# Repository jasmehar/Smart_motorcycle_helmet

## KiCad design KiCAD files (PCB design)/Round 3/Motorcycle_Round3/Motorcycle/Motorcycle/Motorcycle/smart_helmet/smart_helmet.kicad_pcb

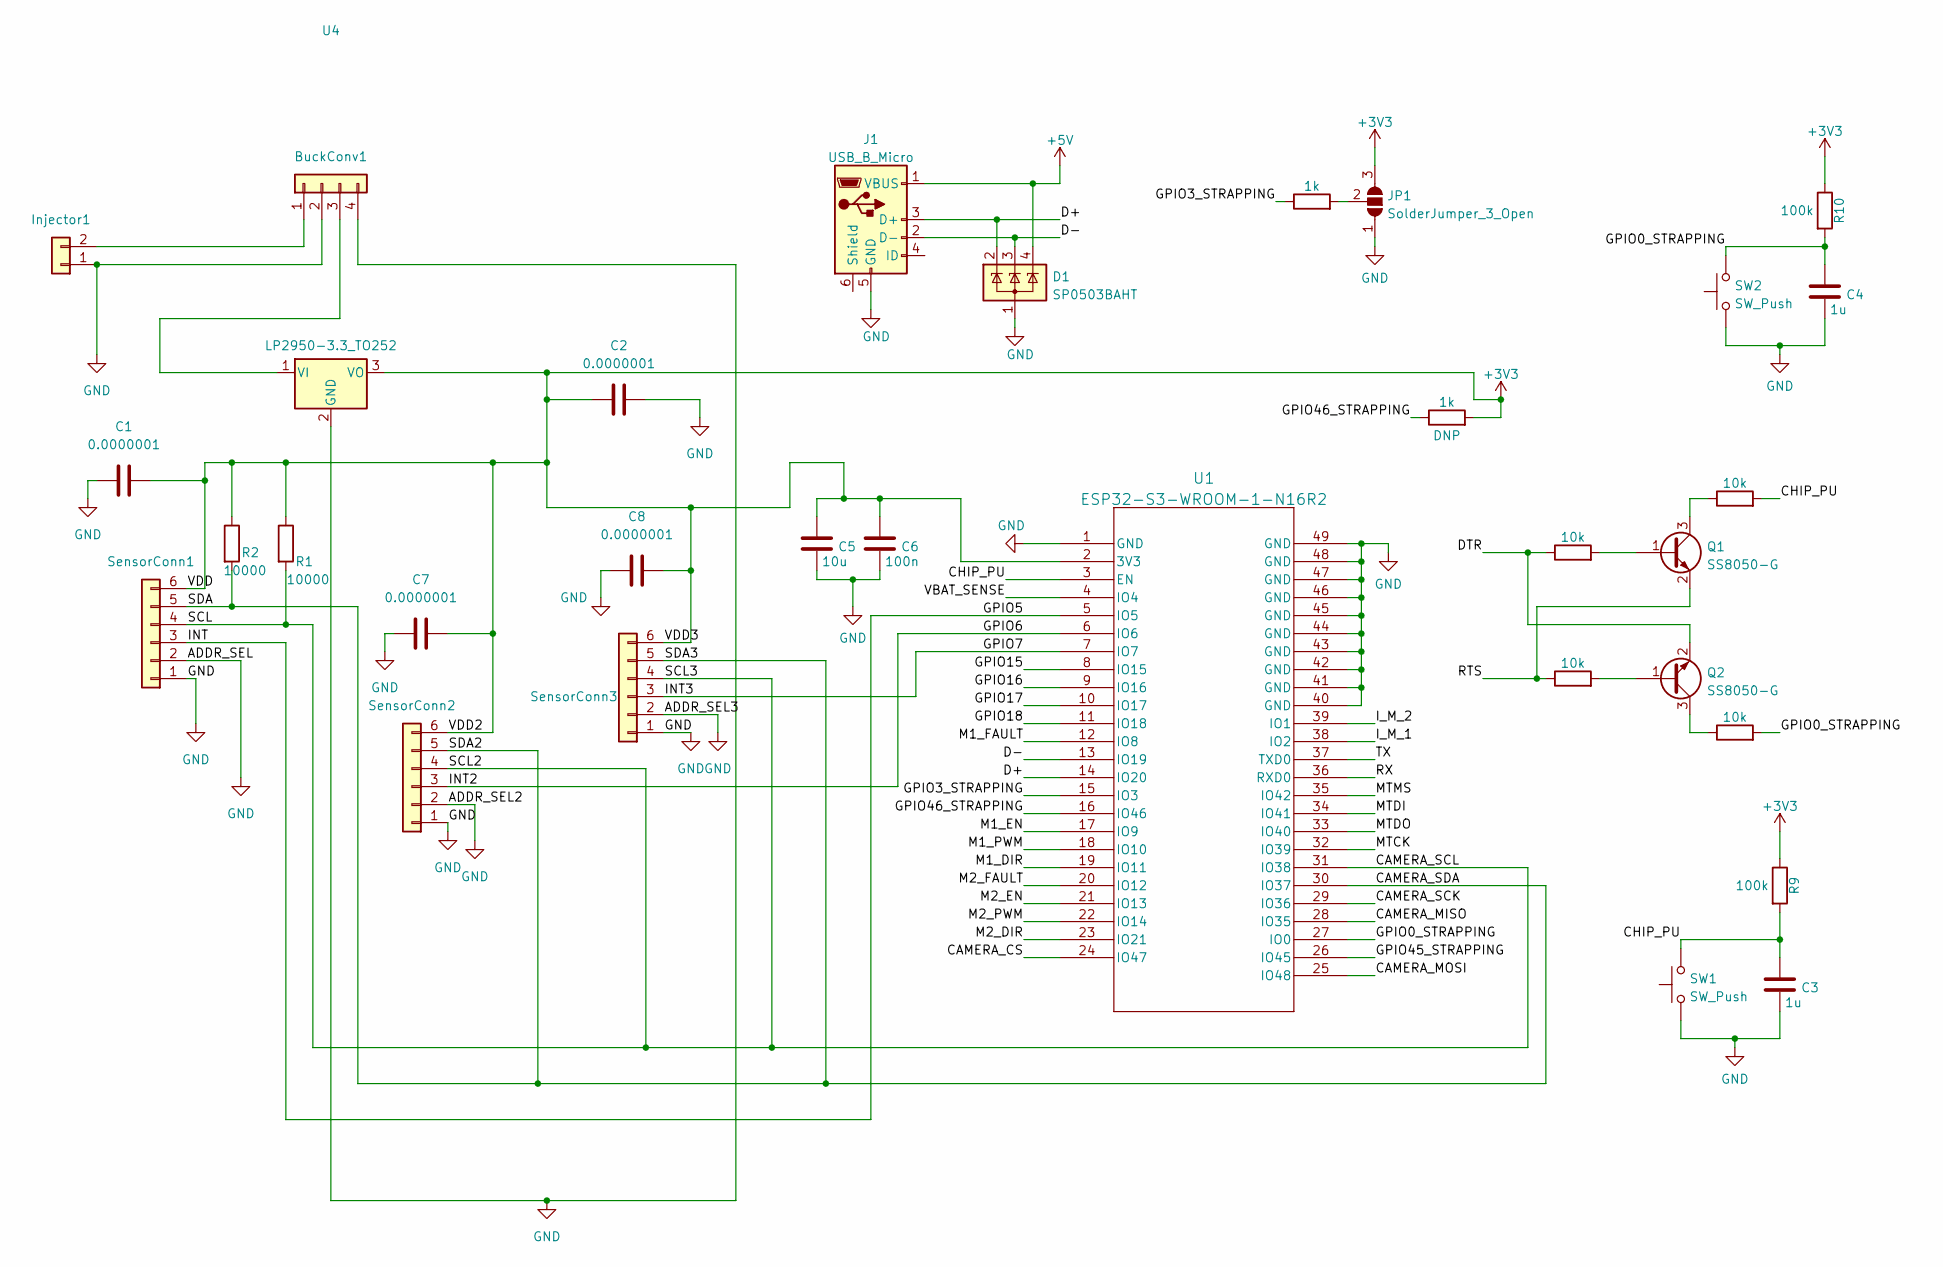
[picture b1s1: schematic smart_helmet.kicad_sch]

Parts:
BuckConv1: Conn_01x04; Molex_KK-254_AE-6410-04A_1x04_P2.54mm_Vertical
C1, C2, C7, C8: 0.0000001; C_0805_2012Metric_Pad1.18x1.45mm_HandSolder
C3, C4: 1u; C_0805_2012Metric
C5: 10u; C_0805_2012Metric
C6: 100n; C_0805_2012Metric
D1: SP0503BAHT; SOT-143
Injector1: Conn_01x02; Molex_KK-254_AE-6410-02A_1x02_P2.54mm_Vertical
J1: USB_B_Micro; USB_Micro-B_Amphenol_10118194_Horizontal
JP1: SolderJumper_3_Open; SolderJumper-3_P2.0mm_Open_TrianglePad1.0x1.5mm
Q1, Q2: SS8050-G; SOT-23
R1, R2: 10000; R_0805_2012Metric_Pad1.20x1.40mm_HandSolder
R3, R6: 1k; R_0805_2012Metric
R4, R5, R7, R8: 10k; R_0805_2012Metric
R9, R10: 100k; R_0805_2012Metric
SW1, SW2: SW_Push; SW_SPST_B3S-1000
SensorConn1, SensorConn2, SensorConn3: Conn_01x06; Molex_KK-254_AE-6410-06A_1x06_P2.54mm_Vertical
U1: ESP32-S3-WROOM-1-N16R2; ESP32-S3-WROOM-1_EXP
U4: LP2950-3.3_TO252; LP3_TEX

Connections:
+3V3: C1.1, C2.1, C5.1, C6.1, C7.1, C8.1, JP1.3 (B), R1.1, R2.1, R3.2, R9.1, R10.1, SensorConn1.6, SensorConn2.6, SensorConn3.6, U1.2 (3V3), U4.3 (VO)
+5V: D1.4 (K), J1.1 (VBUS)
/CAMERA_CS: U1.24 (IO47)
/CAMERA_MISO: U1.28 (IO35)
/CAMERA_MOSI: U1.25 (IO48)
/CAMERA_SCK: U1.29 (IO36)
/CAMERA_SCL: R1.2, SensorConn1.4, SensorConn2.4, SensorConn3.4, U1.31 (IO38)
/CAMERA_SDA: R2.2, SensorConn1.5, SensorConn2.5, SensorConn3.5, U1.30 (IO37)
/CHIP_PU: C3.1, R7.2, R9.2, SW1.2, U1.3 (EN)
/D+: D1.2 (K), J1.3 (D+), U1.14 (IO20)
/D-: D1.3 (K), J1.2 (D-), U1.13 (IO19)
/DTR: Q2.2 (E), R4.1
/GPIO0_STRAPPING: C4.1, R8.2, R10.2, SW2.2, U1.27 (IO0)
/GPIO3_STRAPPING: R6.1, U1.15 (IO3)
/GPIO5: SensorConn1.3, U1.5 (IO5)
/GPIO6: SensorConn2.3, U1.6 (IO6)
/GPIO7: SensorConn3.3, U1.7 (IO7)
/GPIO15: U1.8 (IO15)
/GPIO16: U1.9 (IO16)
/GPIO17: U1.10 (IO17)
/GPIO18: U1.11 (IO18)
/GPIO45_STRAPPING: U1.26 (IO45)
/GPIO46_STRAPPING: R3.1, U1.16 (IO46)
/I_M_1: U1.38 (IO2)
/I_M_2: U1.39 (IO1)
/M1_DIR: U1.19 (IO11)
/M1_EN: U1.17 (IO9)
/M1_FAULT: U1.12 (IO8)
/M1_PWM: U1.18 (IO10)
/M2_DIR: U1.23 (IO21)
/M2_EN: U1.21 (IO13)
/M2_FAULT: U1.20 (IO12)
/M2_PWM: U1.22 (IO14)
/MTCK: U1.32 (IO39)
/MTDI: U1.34 (IO41)
/MTDO: U1.33 (IO40)
/MTMS: U1.35 (IO42)
/RTS: Q1.2 (E), R5.1
/RX: U1.36 (RXD0)
/TX: U1.37 (TXD0)
/VBAT_SENSE: U1.4 (IO4)
GND: BuckConv1.2, BuckConv1.4, C1.2, C2.2, C3.2, C4.2, C5.2, C6.2, C7.2, C8.2, D1.1 (A), Injector1.1, J1.5 (GND), JP1.1 (A), SW1.1, SW2.1, SensorConn1.1, SensorConn1.2, SensorConn2.1, SensorConn2.2, SensorConn3.1, SensorConn3.2, U1.1 (GND), U1.40 (GND), U1.41 (GND), U1.42 (GND), U1.43 (GND), U1.44 (GND), U1.45 (GND), U1.46 (GND), U1.47 (GND), U1.48 (GND), U1.49 (GND), U4.2 (GND)
unnamed: BuckConv1.1, Injector1.2
unnamed: BuckConv1.3, U4.1 (VI)
unnamed: JP1.2 (C), R6.2
unnamed: Q1.1 (B), R4.2
unnamed: Q1.3 (C), R7.1
unnamed: Q2.1 (B), R5.2
unnamed: Q2.3 (C), R8.1

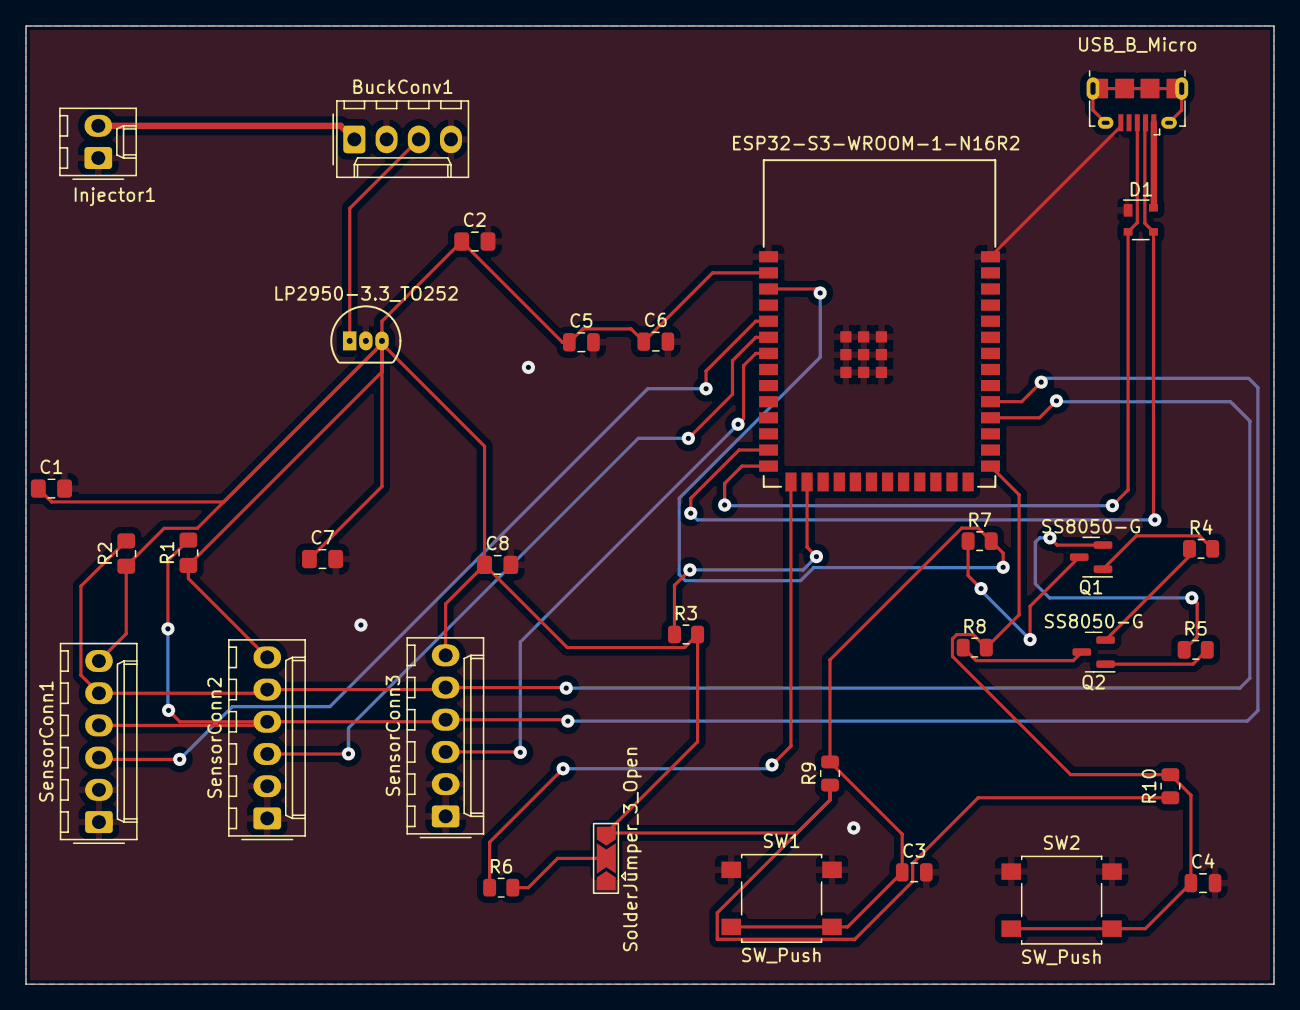
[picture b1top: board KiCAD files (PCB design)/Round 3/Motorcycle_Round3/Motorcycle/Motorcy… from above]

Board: 2 copper layers, 98.4 x 75.6 mm, 32 parts (0 on the bottom side), 23 nets.

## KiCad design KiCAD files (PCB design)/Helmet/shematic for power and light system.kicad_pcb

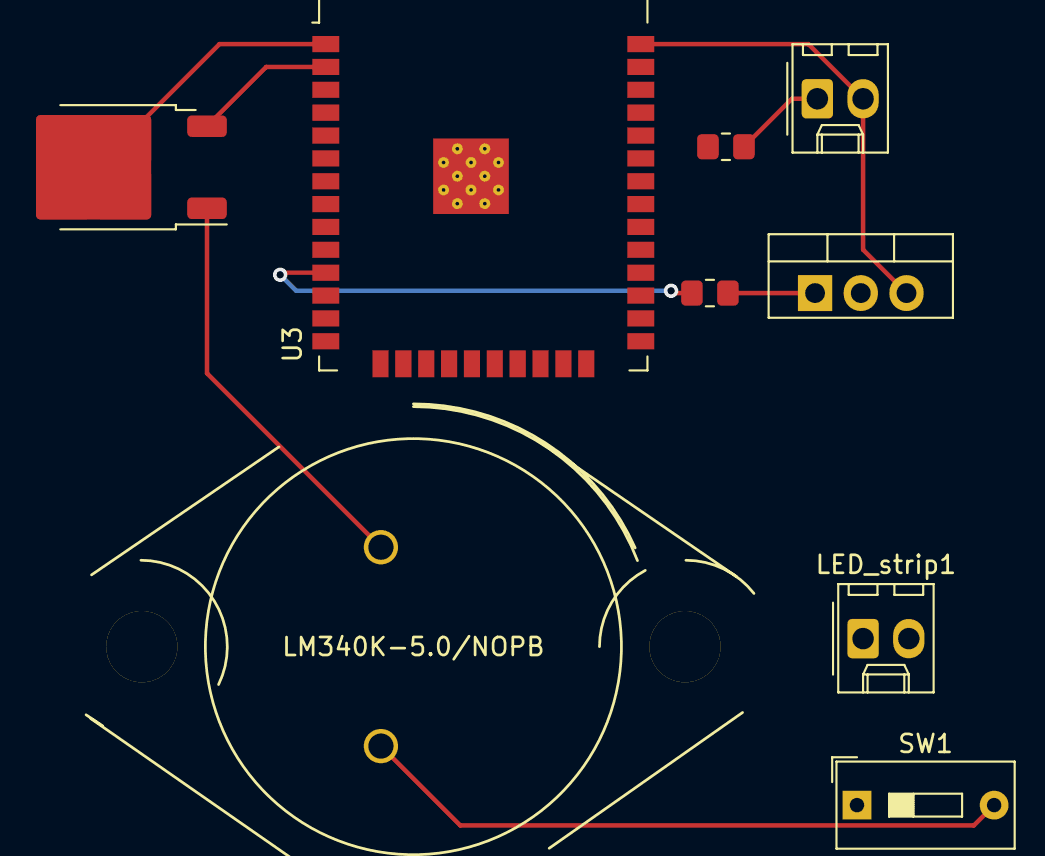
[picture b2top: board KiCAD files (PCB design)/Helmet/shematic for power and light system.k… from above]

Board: 2 copper layers, 9 parts (0 on the bottom side), 8 nets.

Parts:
J1: LED; Molex_KK-254_AE-6410-02A_1x02_P2.54mm_Vertical
LED_strip1: Molex_KK-254_AE-6410-02A_1x02_P2.54mm_Vertical
Q1: IRLZ44N; TO-220-3_Vertical
R1, R2: R; R_0805_2012Metric_Pad1.20x1.40mm_HandSolder
SW1: SW_DIP_x01; SW_DIP_SPSTx01_Slide_9.78x4.72mm_W7.62mm_P2.54mm
U1: LM340K-5.0/NOPB; LM340K-5.0&slash_NOPB
U2: LP2950-3.3_TO252; TO-252-2
U3: ESP32-WROOM-32

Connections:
GND: J1.2, Q1.3 (S), U1.3 (GND), U2.2 (GND), U3.1 (GND), U3.15 (GND), U3.38 (GND), U3.39 (GND)
unnamed: J1.1, R2.2
unnamed: Q1.1 (G), R1.2
unnamed: SW1.2, U1.1 (IN)
unnamed: U1.2 (OUT), U2.1 (VI)
unnamed: U2.3 (VO), U3.2 (VDD)
unnamed: R2.1, U3.37 (IO23)
unnamed: R1.1, U3.11 (IO26)

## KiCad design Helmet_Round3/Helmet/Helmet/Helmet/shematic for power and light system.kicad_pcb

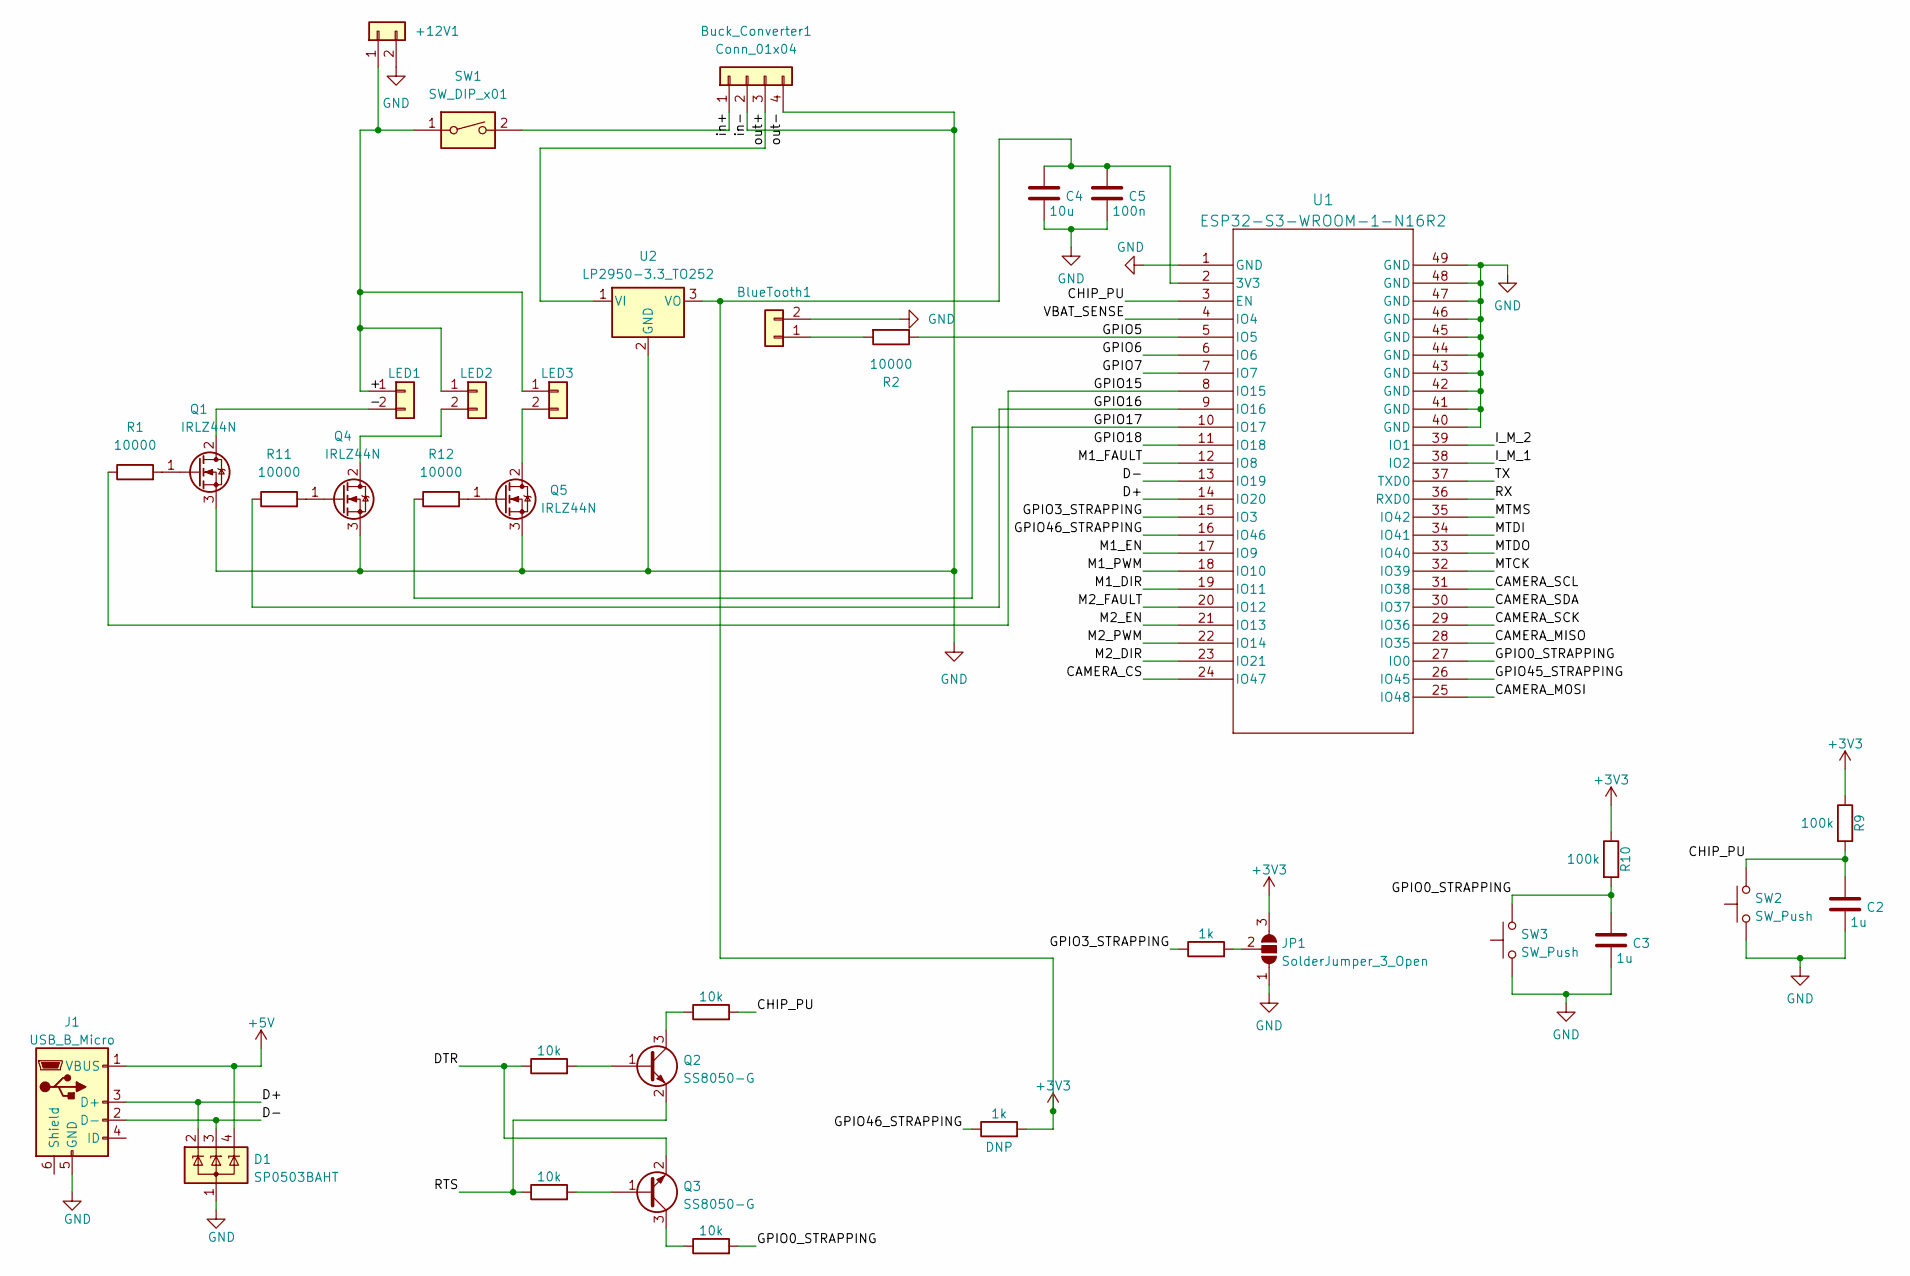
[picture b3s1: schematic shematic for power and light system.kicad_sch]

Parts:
+12V1: Conn_01x02; Molex_KK-254_AE-6410-02A_1x02_P2.54mm_Vertical
BlueTooth1: LED; Molex_KK-254_AE-6410-02A_1x02_P2.54mm_Vertical
Buck_Converter1: Conn_01x04; Molex_KK-254_AE-6410-04A_1x04_P2.54mm_Vertical
C2, C3: 1u; C_0805_2012Metric
C4: 10u; C_0805_2012Metric
C5: 100n; C_0805_2012Metric
D1: SP0503BAHT; SOT-143
J1: USB_B_Micro; USB_Micro-B_Amphenol_10118194_Horizontal
JP1: SolderJumper_3_Open; SolderJumper-3_P2.0mm_Open_TrianglePad1.0x1.5mm
LED1, LED2, LED3: Conn_01x02; Molex_KK-254_AE-6410-02A_1x02_P2.54mm_Vertical
Q1, Q4, Q5: IRLZ44N; PG-TO220-3_INF
Q2, Q3: SS8050-G; SOT-23
R1, R2, R11, R12: 10000; R_0805_2012Metric_Pad1.20x1.40mm_HandSolder
R3, R6: 1k; R_0805_2012Metric
R4, R5, R7, R8: 10k; R_0805_2012Metric
R9, R10: 100k; R_0805_2012Metric
SW1: SW_DIP_x01; SW_DIP_SPSTx01_Slide_9.78x4.72mm_W7.62mm_P2.54mm
SW2, SW3: SW_Push; SW_SPST_B3S-1000
U1: ESP32-S3-WROOM-1-N16R2; ESP32-S3-WROOM-1_EXP
U2: LP2950-3.3_TO252; LP3_TEX

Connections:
+3V3: C4.1, C5.1, JP1.3 (B), R3.2, R9.1, R10.1, U1.2 (3V3), U2.3 (VO)
+5V: D1.4 (K), J1.1 (VBUS)
/+: +12V1.1, LED1.1, LED2.1, LED3.1, SW1.1
/-: LED1.2, Q1.2 (D)
/CAMERA_CS: U1.24 (IO47)
/CAMERA_MISO: U1.28 (IO35)
/CAMERA_MOSI: U1.25 (IO48)
/CAMERA_SCK: U1.29 (IO36)
/CAMERA_SCL: U1.31 (IO38)
/CAMERA_SDA: U1.30 (IO37)
/CHIP_PU: C2.1, R7.2, R9.2, SW2.2, U1.3 (EN)
/D+: D1.2 (K), J1.3 (D+), U1.14 (IO20)
/D-: D1.3 (K), J1.2 (D-), U1.13 (IO19)
/DTR: Q3.2 (E), R4.1
/GPIO0_STRAPPING: C3.1, R8.2, R10.2, SW3.2, U1.27 (IO0)
/GPIO3_STRAPPING: R6.1, U1.15 (IO3)
/GPIO5: R2.1, U1.5 (IO5)
/GPIO6: U1.6 (IO6)
/GPIO7: U1.7 (IO7)
/GPIO15: R1.1, U1.8 (IO15)
/GPIO16: R11.1, U1.9 (IO16)
/GPIO17: R12.1, U1.10 (IO17)
/GPIO18: U1.11 (IO18)
/GPIO45_STRAPPING: U1.26 (IO45)
/GPIO46_STRAPPING: R3.1, U1.16 (IO46)
/I_M_1: U1.38 (IO2)
/I_M_2: U1.39 (IO1)
/M1_DIR: U1.19 (IO11)
/M1_EN: U1.17 (IO9)
/M1_FAULT: U1.12 (IO8)
/M1_PWM: U1.18 (IO10)
/M2_DIR: U1.23 (IO21)
/M2_EN: U1.21 (IO13)
/M2_FAULT: U1.20 (IO12)
/M2_PWM: U1.22 (IO14)
/MTCK: U1.32 (IO39)
/MTDI: U1.34 (IO41)
/MTDO: U1.33 (IO40)
/MTMS: U1.35 (IO42)
/RTS: Q2.2 (E), R5.1
/RX: U1.36 (RXD0)
/TX: U1.37 (TXD0)
/VBAT_SENSE: U1.4 (IO4)
/in+: Buck_Converter1.1, SW1.2
/out+: Buck_Converter1.3, U2.1 (VI)
GND: +12V1.2, BlueTooth1.2, Buck_Converter1.2, Buck_Converter1.4, C2.2, C3.2, C4.2, C5.2, D1.1 (A), J1.5 (GND), JP1.1 (A), Q1.3 (S), Q4.3 (S), Q5.3 (S), SW2.1, SW3.1, U1.1 (GND), U1.40 (GND), U1.41 (GND), U1.42 (GND), U1.43 (GND), U1.44 (GND), U1.45 (GND), U1.46 (GND), U1.47 (GND), U1.48 (GND), U1.49 (GND), U2.2 (GND)
unnamed: BlueTooth1.1, R2.2
unnamed: JP1.2 (C), R6.2
unnamed: LED2.2, Q4.2 (D)
unnamed: LED3.2, Q5.2 (D)
unnamed: Q1.1 (G), R1.2
unnamed: Q2.1 (B), R4.2
unnamed: Q2.3 (C), R7.1
unnamed: Q3.1 (B), R5.2
unnamed: Q3.3 (C), R8.1
unnamed: Q4.1 (G), R11.2
unnamed: Q5.1 (G), R12.2

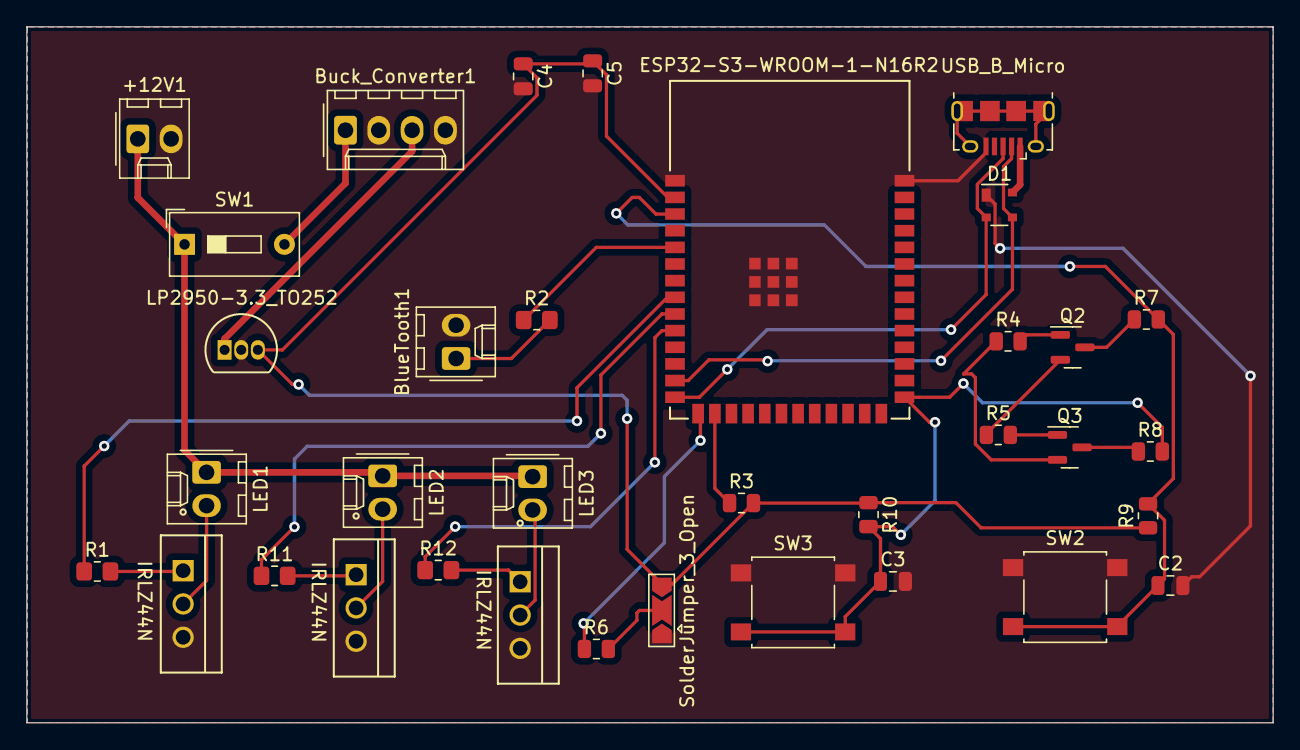
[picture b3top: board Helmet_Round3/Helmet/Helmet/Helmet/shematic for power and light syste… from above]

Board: 2 copper layers, 95.0 x 53.1 mm, 35 parts (0 on the bottom side), 30 nets.

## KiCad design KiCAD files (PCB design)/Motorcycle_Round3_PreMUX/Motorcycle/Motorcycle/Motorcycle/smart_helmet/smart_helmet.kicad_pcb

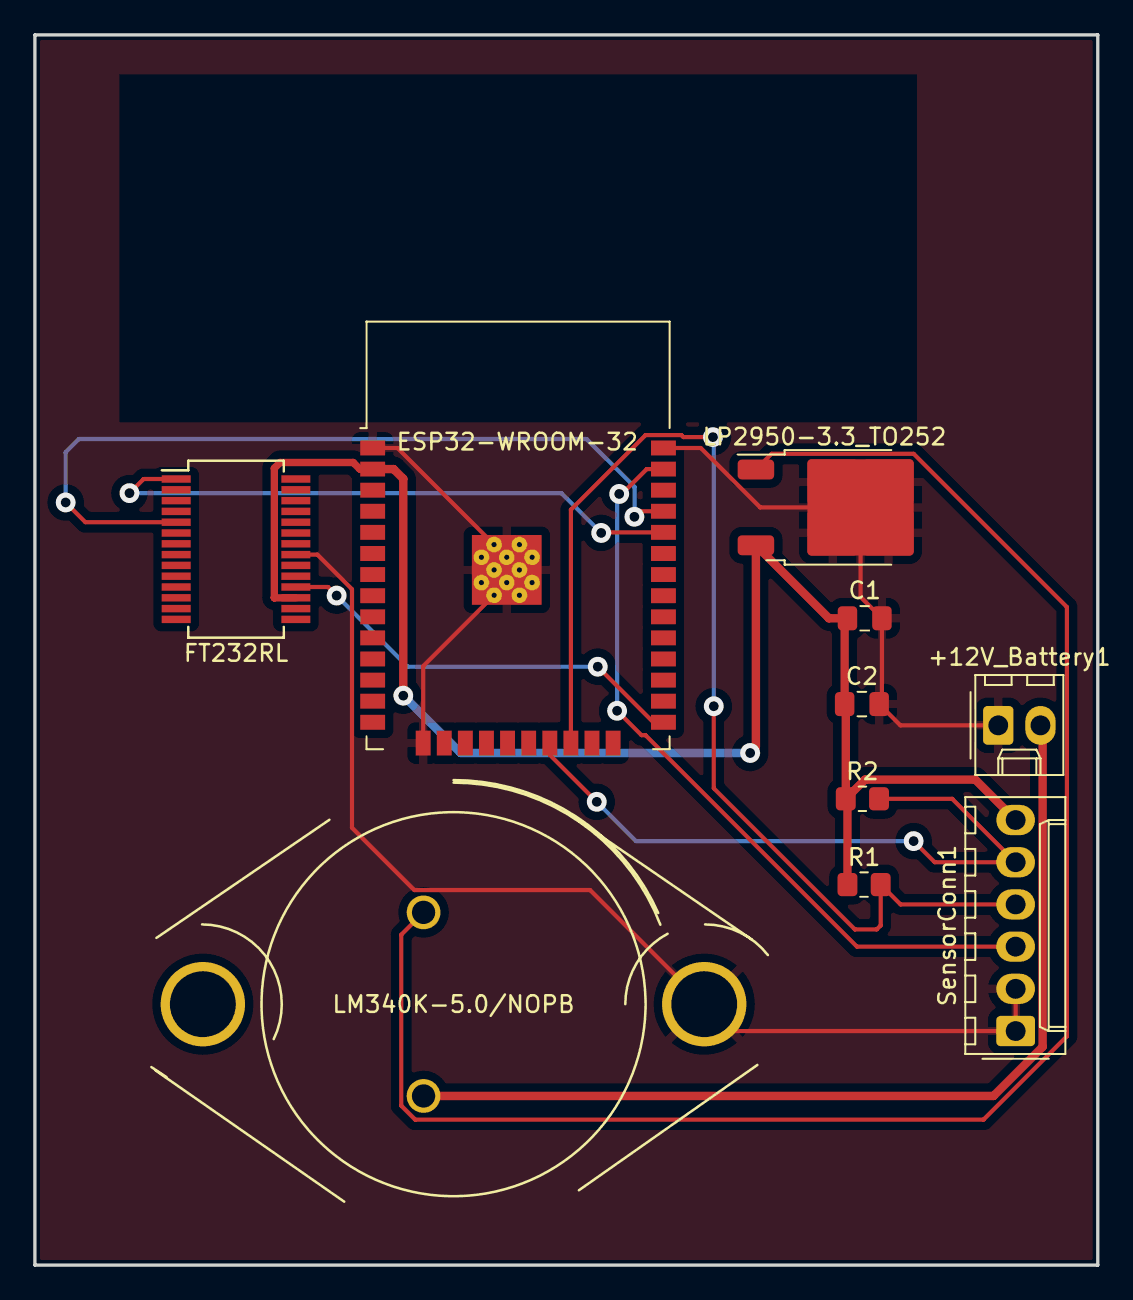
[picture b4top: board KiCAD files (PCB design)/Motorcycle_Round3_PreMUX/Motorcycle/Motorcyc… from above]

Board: 2 copper layers, 64.0 x 74.0 mm, 10 parts (0 on the bottom side), 10 nets.

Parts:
+12V_Battery1: Conn_01x02; Molex_KK-254_AE-6410-02A_1x02_P2.54mm_Vertical
C1, C2: 0.0000001; C_0805_2012Metric_Pad1.18x1.45mm_HandSolder
R1, R2: 10000; R_0805_2012Metric_Pad1.20x1.40mm_HandSolder
SensorConn1: Conn_01x06; Molex_KK-254_AE-6410-06A_1x06_P2.54mm_Vertical
U1: FT232RL; SSOP-28_5.3x10.2mm_P0.65mm
U3: LM340K-5.0/NOPB; LM340K-5.0&slash_NOPB
U4: LP2950-3.3_TO252; TO-252-2
U5: ESP32-WROOM-32

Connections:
/INT: SensorConn1.3, U5.37 (IO23)
/SCL: R1.2, SensorConn1.4, U5.22 (SDI/SD1)
/SDA: R2.2, SensorConn1.5, U5.21 (SDO/SD0)
/VDD: C1.1, C2.1, R1.1, R2.1, SensorConn1.6, U1.17 (3V3OUT), U4.3 (VO), U5.2 (VDD)
GND: +12V_Battery1.1, C1.2, C2.2, SensorConn1.1, SensorConn1.2, U1.21 (GND), U3.3 (GND), U4.2 (GND), U5.1 (GND), U5.15 (GND), U5.38 (GND), U5.39 (GND)
unnamed: +12V_Battery1.2, U3.1 (IN)
unnamed: U1.5 (RXD), U5.35 (TXD0/IO1)
unnamed: U1.1 (TXD), U5.34 (RXD0/IO3)
unnamed: U3.2 (OUT), U4.1 (VI)
unnamed: U1.18 (GND), U5.25 (IO0)

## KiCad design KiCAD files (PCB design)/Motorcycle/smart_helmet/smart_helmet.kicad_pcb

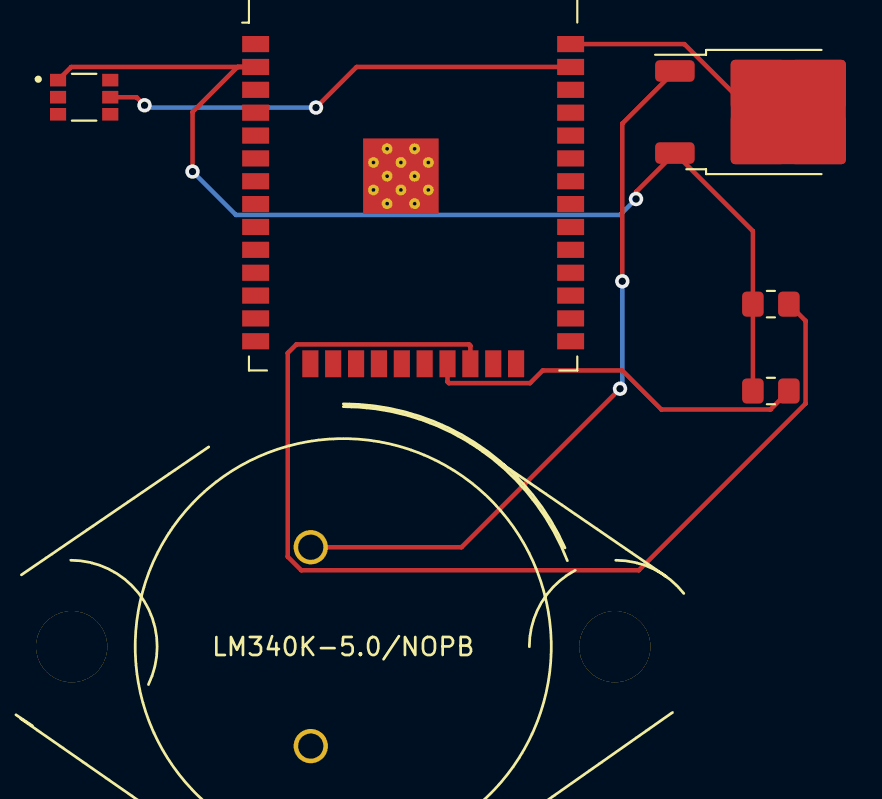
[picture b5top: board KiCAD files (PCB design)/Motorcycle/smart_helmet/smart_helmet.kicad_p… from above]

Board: 2 copper layers, 6 parts (0 on the bottom side), 6 nets.

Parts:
R1, R2: 10000; R_0805_2012Metric_Pad1.20x1.40mm_HandSolder
U2: TSL2561; XDCR_TSL2561
U3: LM340K-5.0/NOPB; LM340K-5.0&slash_NOPB
U4: LP2950-3.3_TO252; TO-252-2
U5: ESP32-WROOM-32

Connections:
GND: U2.2 (ADDR_SEL), U2.3 (GND), U3.3 (GND), U4.2 (GND), U5.1 (GND), U5.15 (GND), U5.38 (GND), U5.39 (GND)
unnamed: U2.5 (INT), U5.37 (IO23)
unnamed: R1.2, U2.4 (SCL), U5.22 (SDI/SD1)
unnamed: R2.2, U2.6 (SDA), U5.21 (SDO/SD0)
unnamed: R1.1, R2.1, U2.1 (VDD), U4.3 (VO), U5.2 (VDD)
unnamed: U3.2 (OUT), U4.1 (VI)

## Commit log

2024-02-16 meeting added
2024-02-29 adding inital design schematics
2024-02-29 adding inital pcb schematics
2024-03-01 first draft PCB done
2024-03-28 finished 3rd round of PCB added buck converter connector
2024-03-30 motorcycle ESP programming done
2024-04-01 deciding to use Arduino instead cuz no way in hell am I using ESP-IDF until I get more time
2024-04-02 all of motorcycle code is done
2024-04-11 all code done
2024-04-30 last commit worked fully this one works with user input
2024-05-02 add final

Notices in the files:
parts and their libraries:
Copyright 2016 Accelerated Designs. All rights reserved.
